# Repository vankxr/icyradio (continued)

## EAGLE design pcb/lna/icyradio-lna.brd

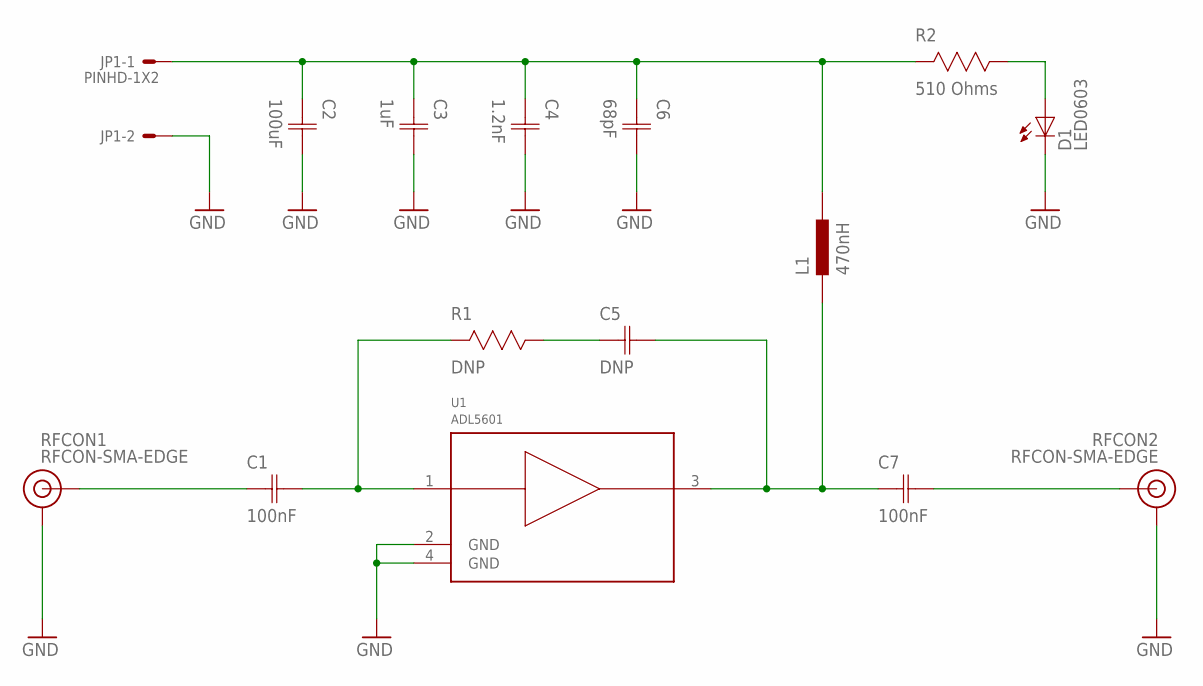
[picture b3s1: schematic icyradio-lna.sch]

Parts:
C1, C7: 100nF; CAP0603
C2: 100uF; CAP1206
C3: 1uF; CAP0603
C4: 1.2nF; CAP0603
C5: DNP; CAP0603
C6: 68pF; CAP0603
D1: LED0603; 0603
JP1: PINHD-1X2; 1X02
L1: 470nH; IND0603
R1: DNP; RES0603
R2: 510 Ohms; RES0603
RFCON1, RFCON2: RFCON-SMA-EDGE; SMA-EDGE
U1: ADL5601; SOT89

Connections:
GND: C2.2 (C2), C3.2 (C2), C4.2 (C2), C6.2 (C2), D1.C, JP1.2, RFCON1.GND@0 (GND), RFCON1.GND@1 (GND), RFCON1.GND@2 (GND), RFCON1.GND@3 (GND), RFCON2.GND@0 (GND), RFCON2.GND@1 (GND), RFCON2.GND@2 (GND), RFCON2.GND@3 (GND), U1.2 (GND), U1.4 (GND)
unnamed: C5.1 (C1), R1.1
unnamed: D1.A, R2.1
RFIN: C1.1 (C1), RFCON1.SIG (SIGNAL)
RFOUT: C7.2 (C2), RFCON2.SIG (SIGNAL)
TXPA_IN: C1.2 (C2), R1.2, U1.1 (RFIN)
TXPA_OUT: C5.2 (C2), C7.1 (C1), L1.1, U1.3 (RFOUT)
VDD: C2.1 (C1), C3.1 (C1), C4.1 (C1), C6.1 (C1), JP1.1, L1.2, R2.2

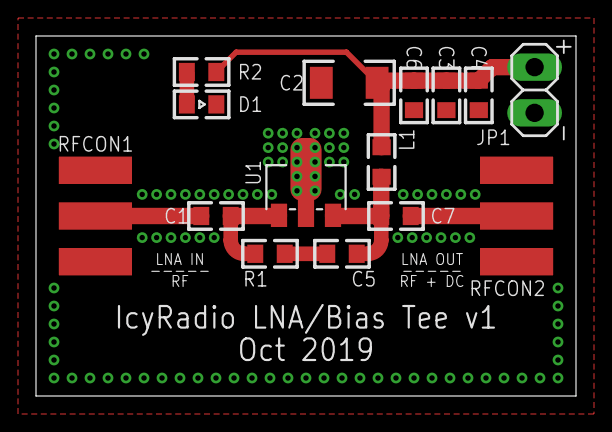
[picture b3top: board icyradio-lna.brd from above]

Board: 2 copper layers, 30.0 x 20.0 mm, 15 parts (0 on the bottom side), 8 nets.

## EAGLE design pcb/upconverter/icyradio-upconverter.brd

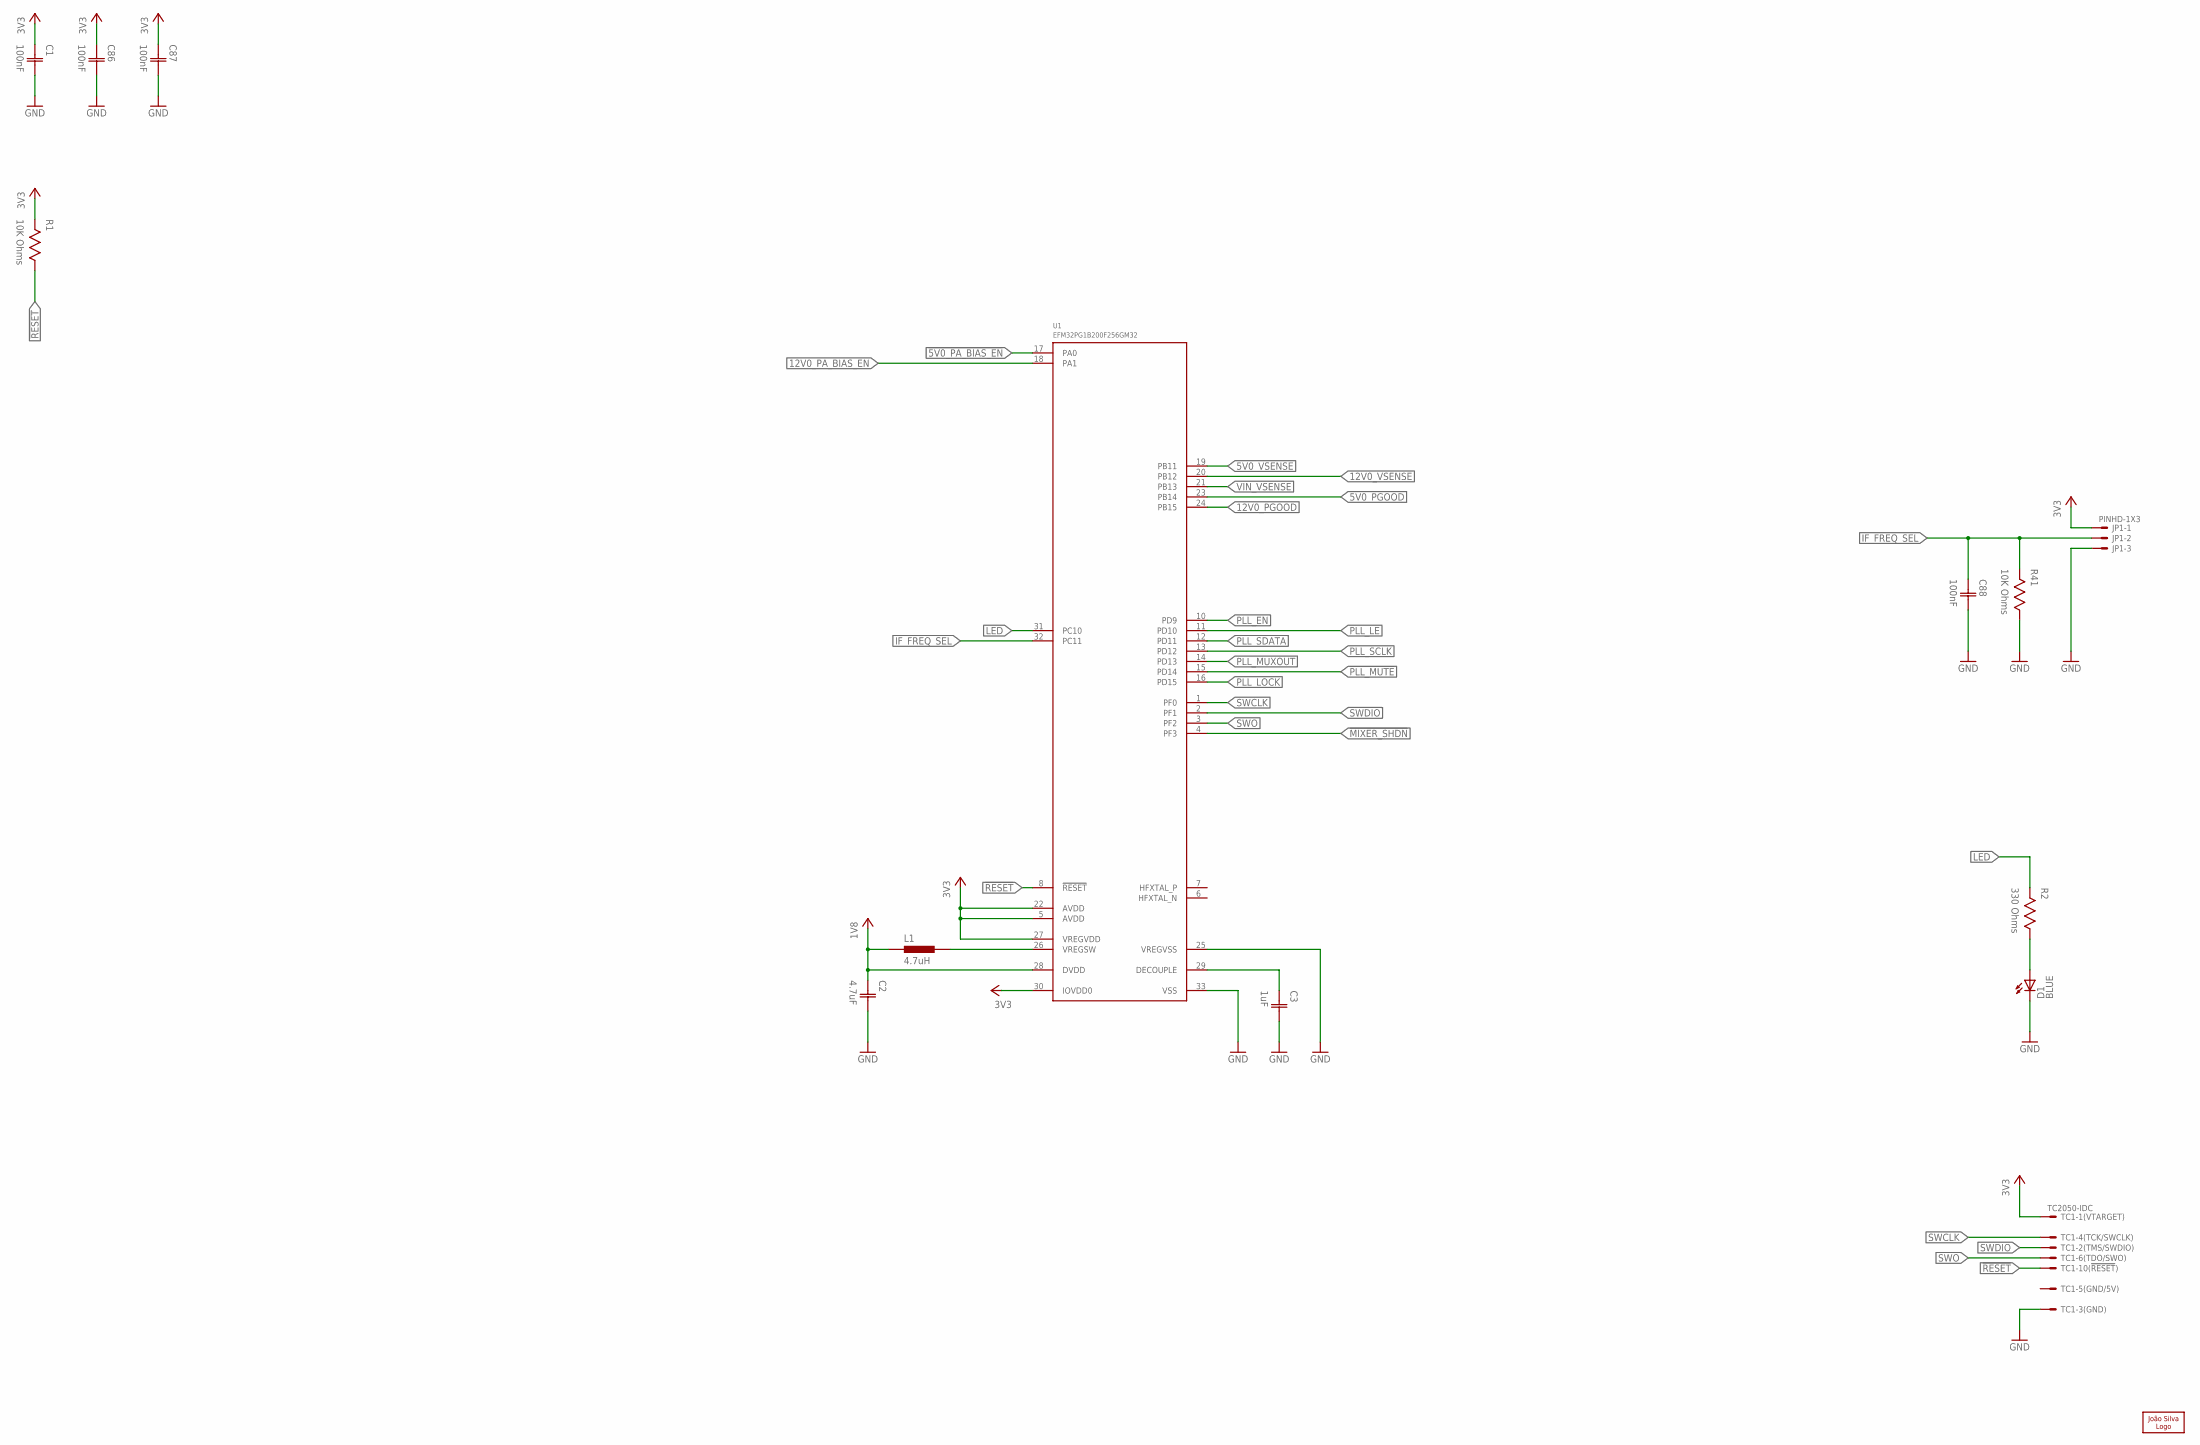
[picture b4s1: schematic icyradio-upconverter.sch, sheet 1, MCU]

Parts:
C1, C86, C87, C88: 100nF; CAP0603
C2: 4.7uF; CAP0603
C3: 1uF; CAP0603
D1: LED0603; 0603
JP1: PINHD-1X3; 1X03
L1: 4.7uH; IND0603
LOGO1: JS-5MM; JS_5MM
R1, R41: 10K Ohms; RES0603
R2: 330 Ohms; RES0603
TC1: TC2050-IDC
U1: EFM32PG1B200F256GM32; QFN32_0.5P_JPG

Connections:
1V8: C2.1 (C1), L1.1, U1.28 (DVDD)
3V3: C1.1 (C1), C86.1 (C1), C87.1 (C1), JP1.1, R1.2, TC1.1, U1.5 (AVDD), U1.22 (AVDD), U1.27 (VREGVDD), U1.30 (IOVDD0); also elsewhere on the board
5V0_PGOOD: U1.23 (PB14); also elsewhere on the board
5V0_VSENSE: U1.19 (PB11); also elsewhere on the board
12V0_PA_BIAS_EN: U1.18 (PA1); also elsewhere on the board
12V0_PGOOD: U1.24 (PB15); also elsewhere on the board
12V0_VSENSE: U1.20 (PB12); also elsewhere on the board
!5V0_PA_BIAS_EN: U1.17 (PA0); also elsewhere on the board
!MIXER_SHDN: U1.4 (PF3); also elsewhere on the board
!PLL_MUTE: U1.15 (PD14); also elsewhere on the board
!RESET: R1.1, TC1.10, U1.8 (!RESET)
GND: C1.2 (C2), C2.2 (C2), C3.2 (C2), C86.2 (C2), C87.2 (C2), C88.2 (C2), D1.C, JP1.3, R41.1, TC1.3, U1.25 (VREGVSS), U1.33 (VSS); also elsewhere on the board
IF_FREQ_SEL: C88.1 (C1), JP1.2, R41.2, U1.32 (PC11)
LED: R2.2, U1.31 (PC10)
unnamed: L1.2, U1.26 (VREGSW)
unnamed: C3.1 (C1), U1.29 (DECOUPLE)
unnamed: D1.A, R2.1
PLL_EN: U1.10 (PD9); also elsewhere on the board
PLL_LE: U1.11 (PD10); also elsewhere on the board
PLL_LOCK: U1.16 (PD15); also elsewhere on the board
PLL_MUXOUT: U1.14 (PD13); also elsewhere on the board
PLL_SCLK: U1.13 (PD12); also elsewhere on the board
PLL_SDATA: U1.12 (PD11); also elsewhere on the board
SWCLK: TC1.4, U1.1 (PF0)
SWDIO: TC1.2, U1.2 (PF1)
SWO: TC1.6, U1.3 (PF2)
VIN_VSENSE: U1.21 (PB13); also elsewhere on the board

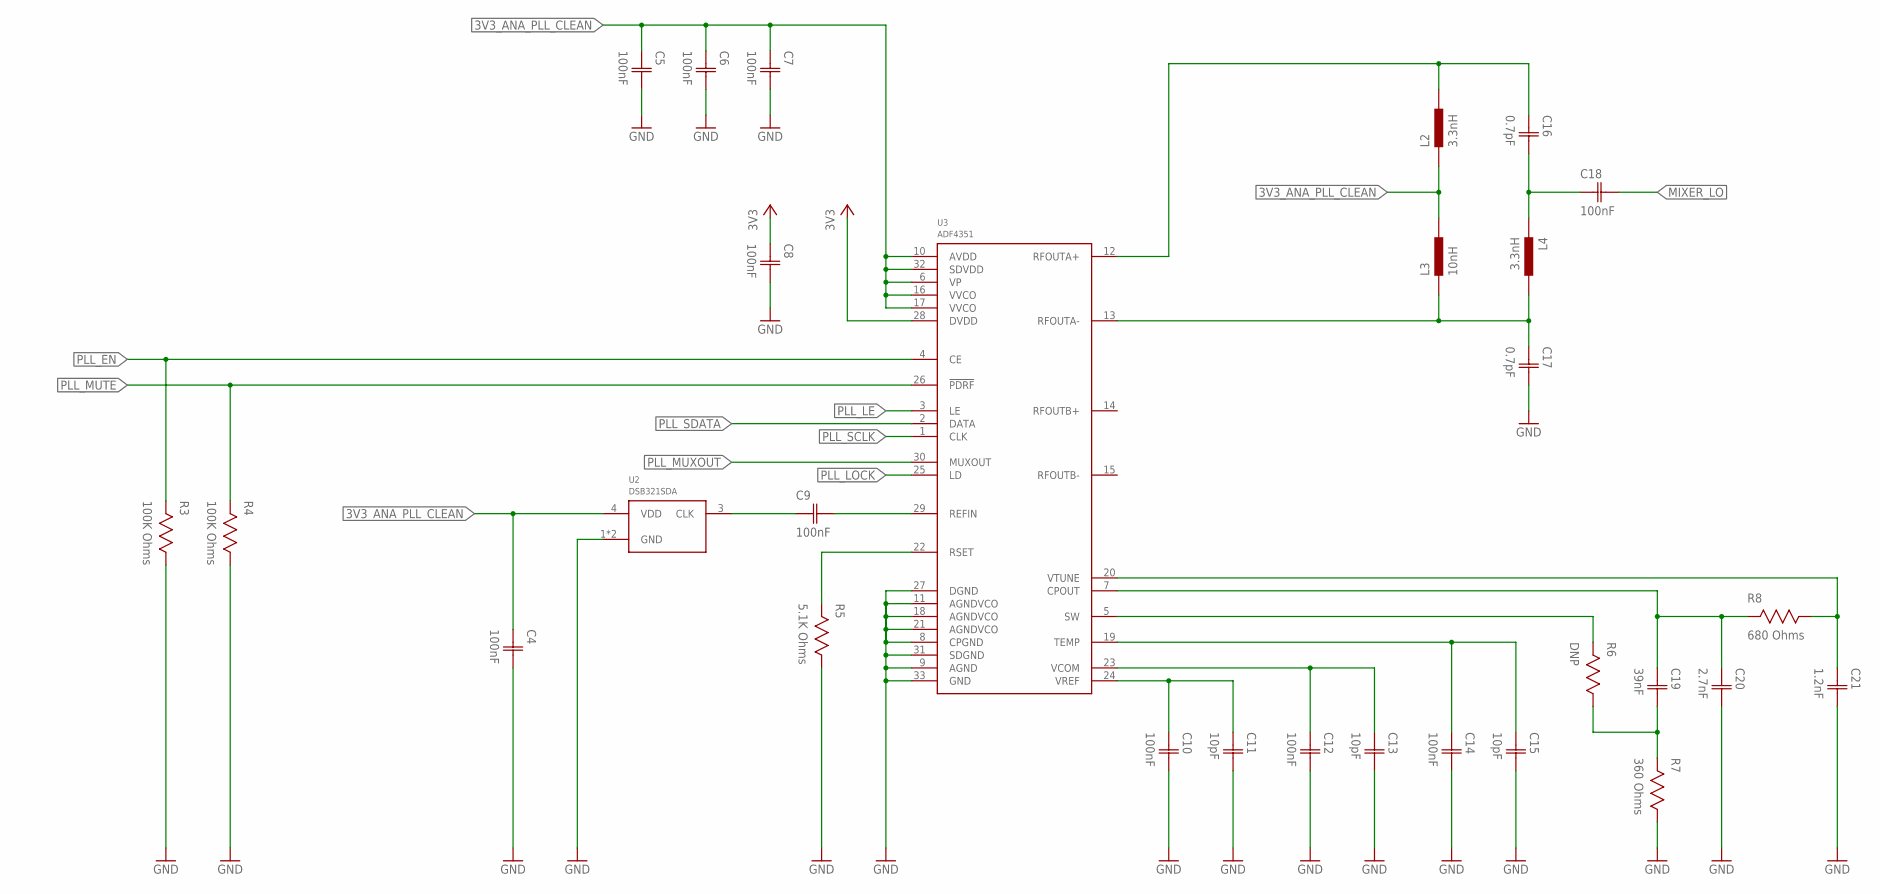
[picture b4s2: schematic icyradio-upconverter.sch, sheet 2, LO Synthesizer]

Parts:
C4, C5, C6, C7, C8, C9, C10, C12, C14, C18: 100nF; CAP0603
C11, C13, C15: 10pF; CAP0603
C16, C17: 0.7pF; CAP0603
C19: 39nF; CAP0603
C20: 2.7nF; CAP0603
C21: 1.2nF; CAP0603
L2, L4: 3.3nH; IND0603
L3: 10nH; IND0603
R3, R4: 100K Ohms; RES0603
R5: 5.1K Ohms; RES0603
R6: DNP; RES0603
R7: 360 Ohms; RES0603
R8: 680 Ohms; RES0603
U2: DSB321SDA; TCXO-3225
U3: ADF4351; QFN32

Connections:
3V3: C8.1 (C1), U3.28 (DVDD); also elsewhere on the board
3V3_ANA_PLL_CLEAN: C4.1 (C1), C5.1 (C1), C6.1 (C1), C7.1 (C1), L2.1, L3.2, U2.4 (VDD), U3.6 (VP), U3.10 (AVDD), U3.16 (VVCO), U3.17 (VVCO), U3.32 (SDVDD); also elsewhere on the board
!PLL_MUTE: R4.2, U3.26 (!PDRF); also elsewhere on the board
GND: C4.2 (C2), C5.2 (C2), C6.2 (C2), C7.2 (C2), C8.2 (C2), C10.2 (C2), C11.2 (C2), C12.2 (C2), C13.2 (C2), C14.2 (C2), C15.2 (C2), C17.2 (C2), C20.2 (C2), C21.2 (C2), R3.1, R4.1, R5.1, R7.1, U2.1 (GND), U2.2 (GND), U3.8 (CPGND), U3.9 (AGND), U3.11 (AGNDVCO), U3.18 (AGNDVCO), U3.21 (AGNDVCO), U3.27 (DGND), U3.31 (SDGND), U3.33 (GND); also elsewhere on the board
MIXER_LO: C18.2 (C2); also elsewhere on the board
unnamed: C16.2 (C2), C18.1 (C1), L4.1
unnamed: C17.1 (C1), L3.1, L4.2, U3.13 (RFOUTA-)
unnamed: C16.1 (C1), L2.2, U3.12 (RFOUTA+)
unnamed: C19.2 (C2), R6.1, R7.2
unnamed: R5.2, U3.22 (RSET)
PLL_CP_VOUT: C19.1 (C1), C20.1 (C1), R8.2, U3.7 (CPOUT)
PLL_EN: R3.2, U3.4 (CE); also elsewhere on the board
PLL_FASTLOCK_SW: R6.2, U3.5 (SW)
PLL_LE: U3.3 (LE); also elsewhere on the board
PLL_LOCK: U3.25 (LD); also elsewhere on the board
PLL_MUXOUT: U3.30 (MUXOUT); also elsewhere on the board
PLL_REF_ACC: C9.2 (C2), U3.29 (REFIN)
PLL_REF_DCC: C9.1 (C1), U2.3 (CLK)
PLL_SCLK: U3.1 (CLK); also elsewhere on the board
PLL_SDATA: U3.2 (DATA); also elsewhere on the board
PLL_TEMP: C14.1 (C1), C15.1 (C1), U3.19 (TEMP)
PLL_VCOM: C12.1 (C1), C13.1 (C1), U3.23 (VCOM)
PLL_VREF: C10.1 (C1), C11.1 (C1), U3.24 (VREF)
PLL_VTUNE: C21.1 (C1), R8.1, U3.20 (VTUNE)

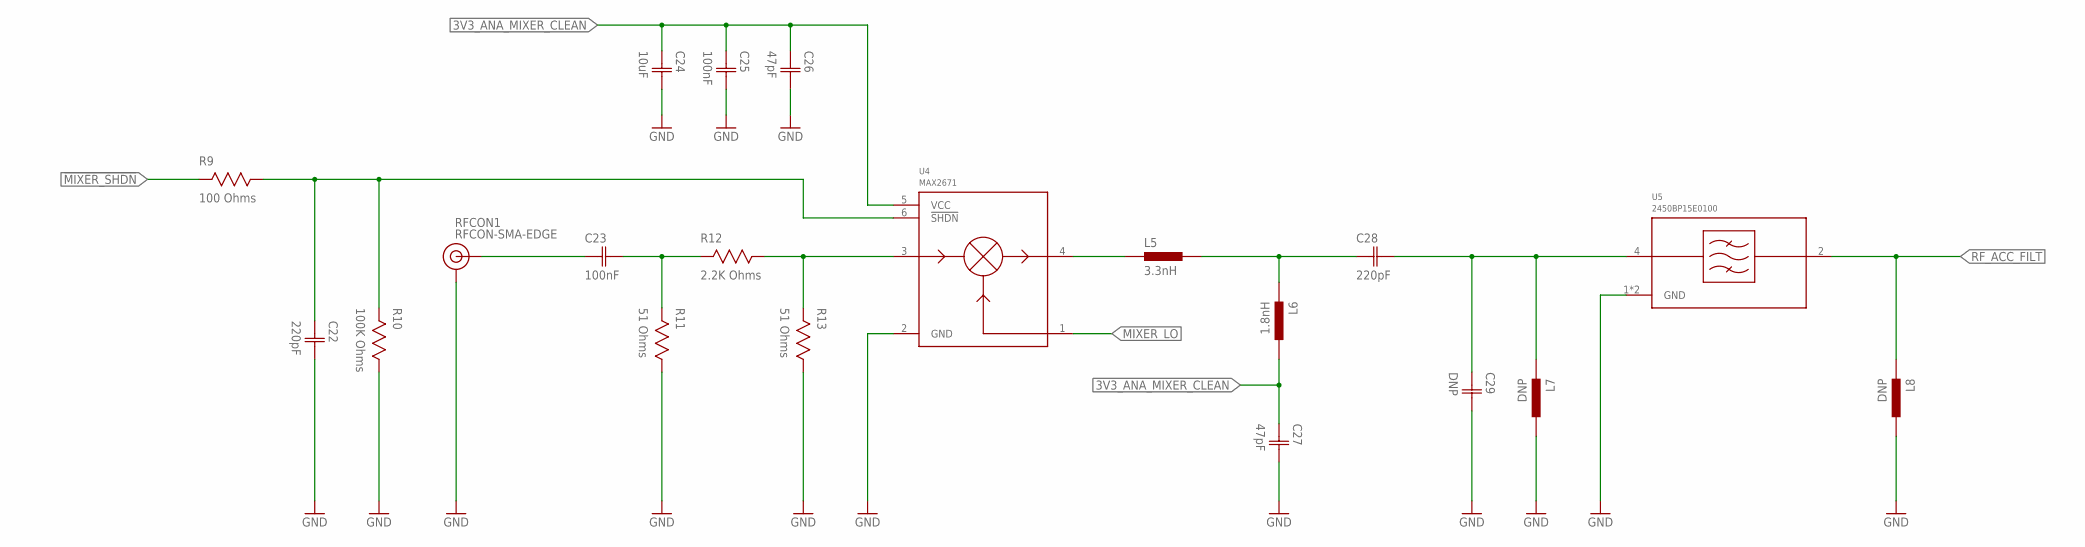
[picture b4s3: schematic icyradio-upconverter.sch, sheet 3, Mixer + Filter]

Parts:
C22, C28: 220pF; CAP0603
C23, C25: 100nF; CAP0603
C24: 10uF; CAP0603
C26, C27: 47pF; CAP0603
C29: DNP; CAP0603
L5: 3.3nH; IND0603
L6: 1.8nH; IND0603
L7, L8: DNP; IND0603
R9: 100 Ohms; RES0603
R10: 100K Ohms; RES0603
R11, R13: 51 Ohms; RES0603
R12: 2.2K Ohms; RES0603
RFCON1: RFCON-SMA-EDGE; SMA-EDGE
U4: MAX2671; SOT23-6
U5: 2450BP15E0100

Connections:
3V3_ANA_MIXER_CLEAN: C24.1 (C1), C25.1 (C1), C26.1 (C1), C27.1 (C1), L6.2, U4.5 (VCC); also elsewhere on the board
!MIXER_SHDN: R9.2; also elsewhere on the board
GND: C22.2 (C2), C24.2 (C2), C25.2 (C2), C26.2 (C2), C27.2 (C2), C29.2 (C2), L7.2, L8.2, R10.1, R11.1, R13.1, RFCON1.GND@0 (GND), RFCON1.GND@1 (GND), RFCON1.GND@2 (GND), RFCON1.GND@3 (GND), U4.2 (GND), U5.1 (GND), U5.3 (GND); also elsewhere on the board
IF_IN_ACC: R12.1, R13.2, U4.3 (IFIN)
IF_IN_DCC: C23.1 (C1), RFCON1.SIG (SIGNAL)
MIXER_LO: U4.1 (LO); also elsewhere on the board
unnamed: C22.1 (C1), R9.1, R10.2, U4.6 (!SHDN)
unnamed: C28.1 (C1), L5.2, L6.1
unnamed: L5.1, U4.4 (RFOUT)
unnamed: C23.2 (C2), R11.2, R12.2
RF_ACC: C28.2 (C2), C29.1 (C1), L7.1, U5.4 (RFIN)
RF_ACC_FILT: L8.1, U5.2 (RFOUT); also elsewhere on the board

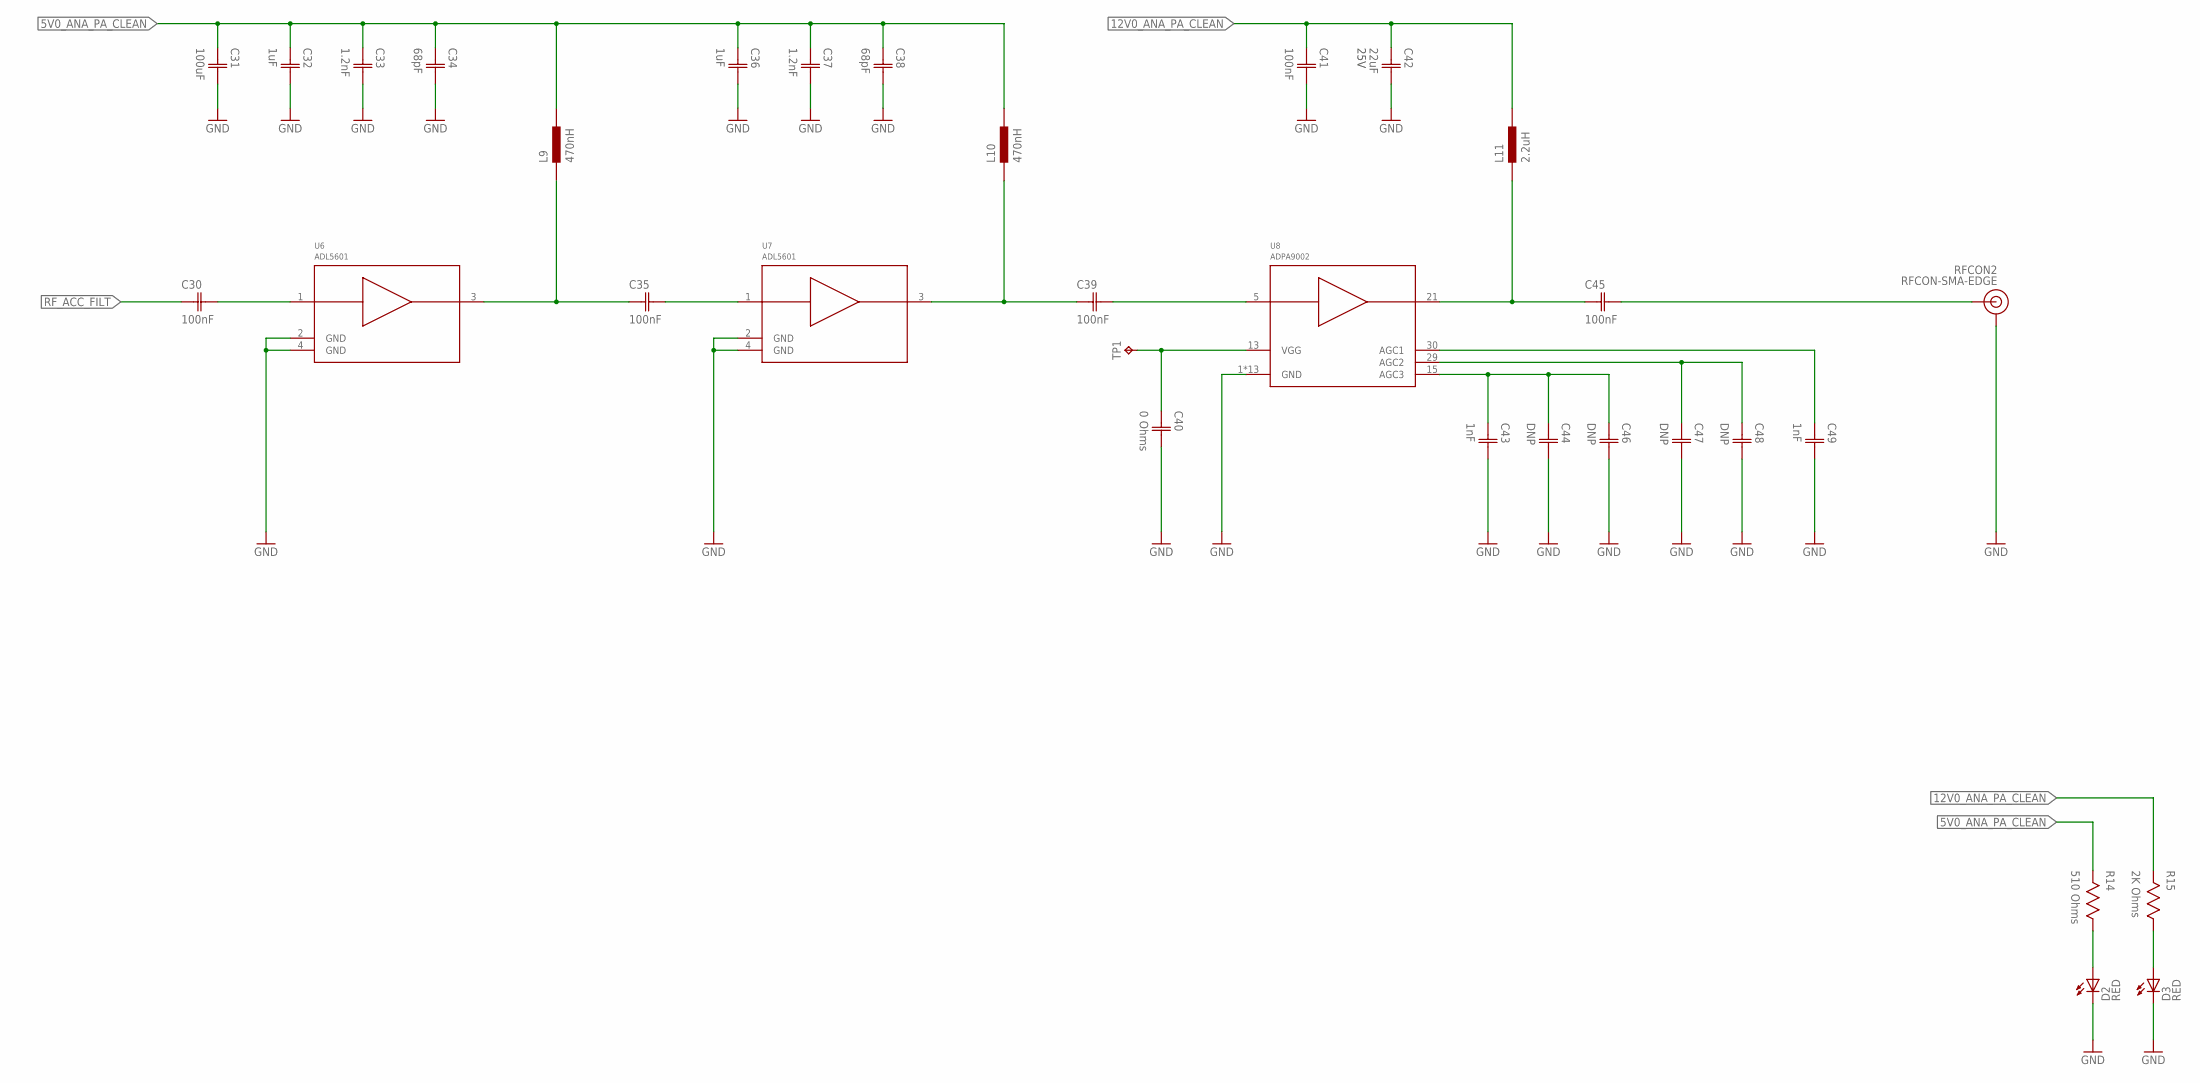
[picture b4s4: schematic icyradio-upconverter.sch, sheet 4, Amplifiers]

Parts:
C30, C35, C39, C41, C45: 100nF; CAP0603
C31: 100uF; CAP1206
C32, C36: 1uF; CAP0603
C33, C37: 1.2nF; CAP0603
C34, C38: 68pF; CAP0603
C40: 0 Ohms; CAP0603
C42: 22uF; CAP1206; VOLTAGE 25V
C43, C49: 1nF; CAP0603
C44, C46, C47, C48: DNP; CAP0603
D2, D3: LED0603; 0603
L9, L10: 470nH; IND0603
L11: 2.2uH; IND0603
R14: 510 Ohms; RES0603
R15: 2K Ohms; RES0603
RFCON2: RFCON-SMA-EDGE; SMA-EDGE
TP1: TESTPOINT-1.27MM; PAD1.27MM
U6, U7: ADL5601; SOT89
U8: ADPA9002; QFN32

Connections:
5V0_ANA_PA_CLEAN: C31.1 (C1), C32.1 (C1), C33.1 (C1), C34.1 (C1), C36.1 (C1), C37.1 (C1), C38.1 (C1), L9.2, L10.2, R14.2; also elsewhere on the board
12V0_ANA_PA_CLEAN: C41.1 (C1), C42.1 (C1), L11.2, R15.2; also elsewhere on the board
GND: C31.2 (C2), C32.2 (C2), C33.2 (C2), C34.2 (C2), C36.2 (C2), C37.2 (C2), C38.2 (C2), C40.2 (C2), C41.2 (C2), C42.2 (C2), C43.2 (C2), C44.2 (C2), C46.2 (C2), C47.2 (C2), C48.2 (C2), C49.2 (C2), D2.C, D3.C, RFCON2.GND@0 (GND), RFCON2.GND@1 (GND), RFCON2.GND@2 (GND), RFCON2.GND@3 (GND), U6.2 (GND), U6.4 (GND), U7.2 (GND), U7.4 (GND), U8.1 (GND), U8.4 (GND), U8.6 (GND), U8.8 (GND), U8.9 (GND), U8.16 (GND), U8.17 (GND), U8.20 (GND), U8.22 (GND), U8.24 (GND), U8.25 (GND), U8.32 (GND), U8.33 (GND); also elsewhere on the board
unnamed: C43.1 (C1), C44.1 (C1), C46.1 (C1), U8.15 (AGC3)
unnamed: C47.1 (C1), C48.1 (C1), U8.29 (AGC2)
unnamed: C49.1 (C1), U8.30 (AGC1)
unnamed: C40.1 (C1), TP1.TP, U8.13 (VGG)
unnamed: C30.2 (C2), U6.1 (RFIN)
unnamed: C45.1 (C1), L11.1, U8.21 (RFOUT)
unnamed: C35.1 (C1), L9.1, U6.3 (RFOUT)
unnamed: C35.2 (C2), U7.1 (RFIN)
unnamed: C39.1 (C1), L10.1, U7.3 (RFOUT)
unnamed: C39.2 (C2), U8.5 (RFIN)
unnamed: C45.2 (C2), RFCON2.SIG (SIGNAL)
unnamed: D2.A, R14.1
unnamed: D3.A, R15.1
RF_ACC_FILT: C30.1 (C1); also elsewhere on the board

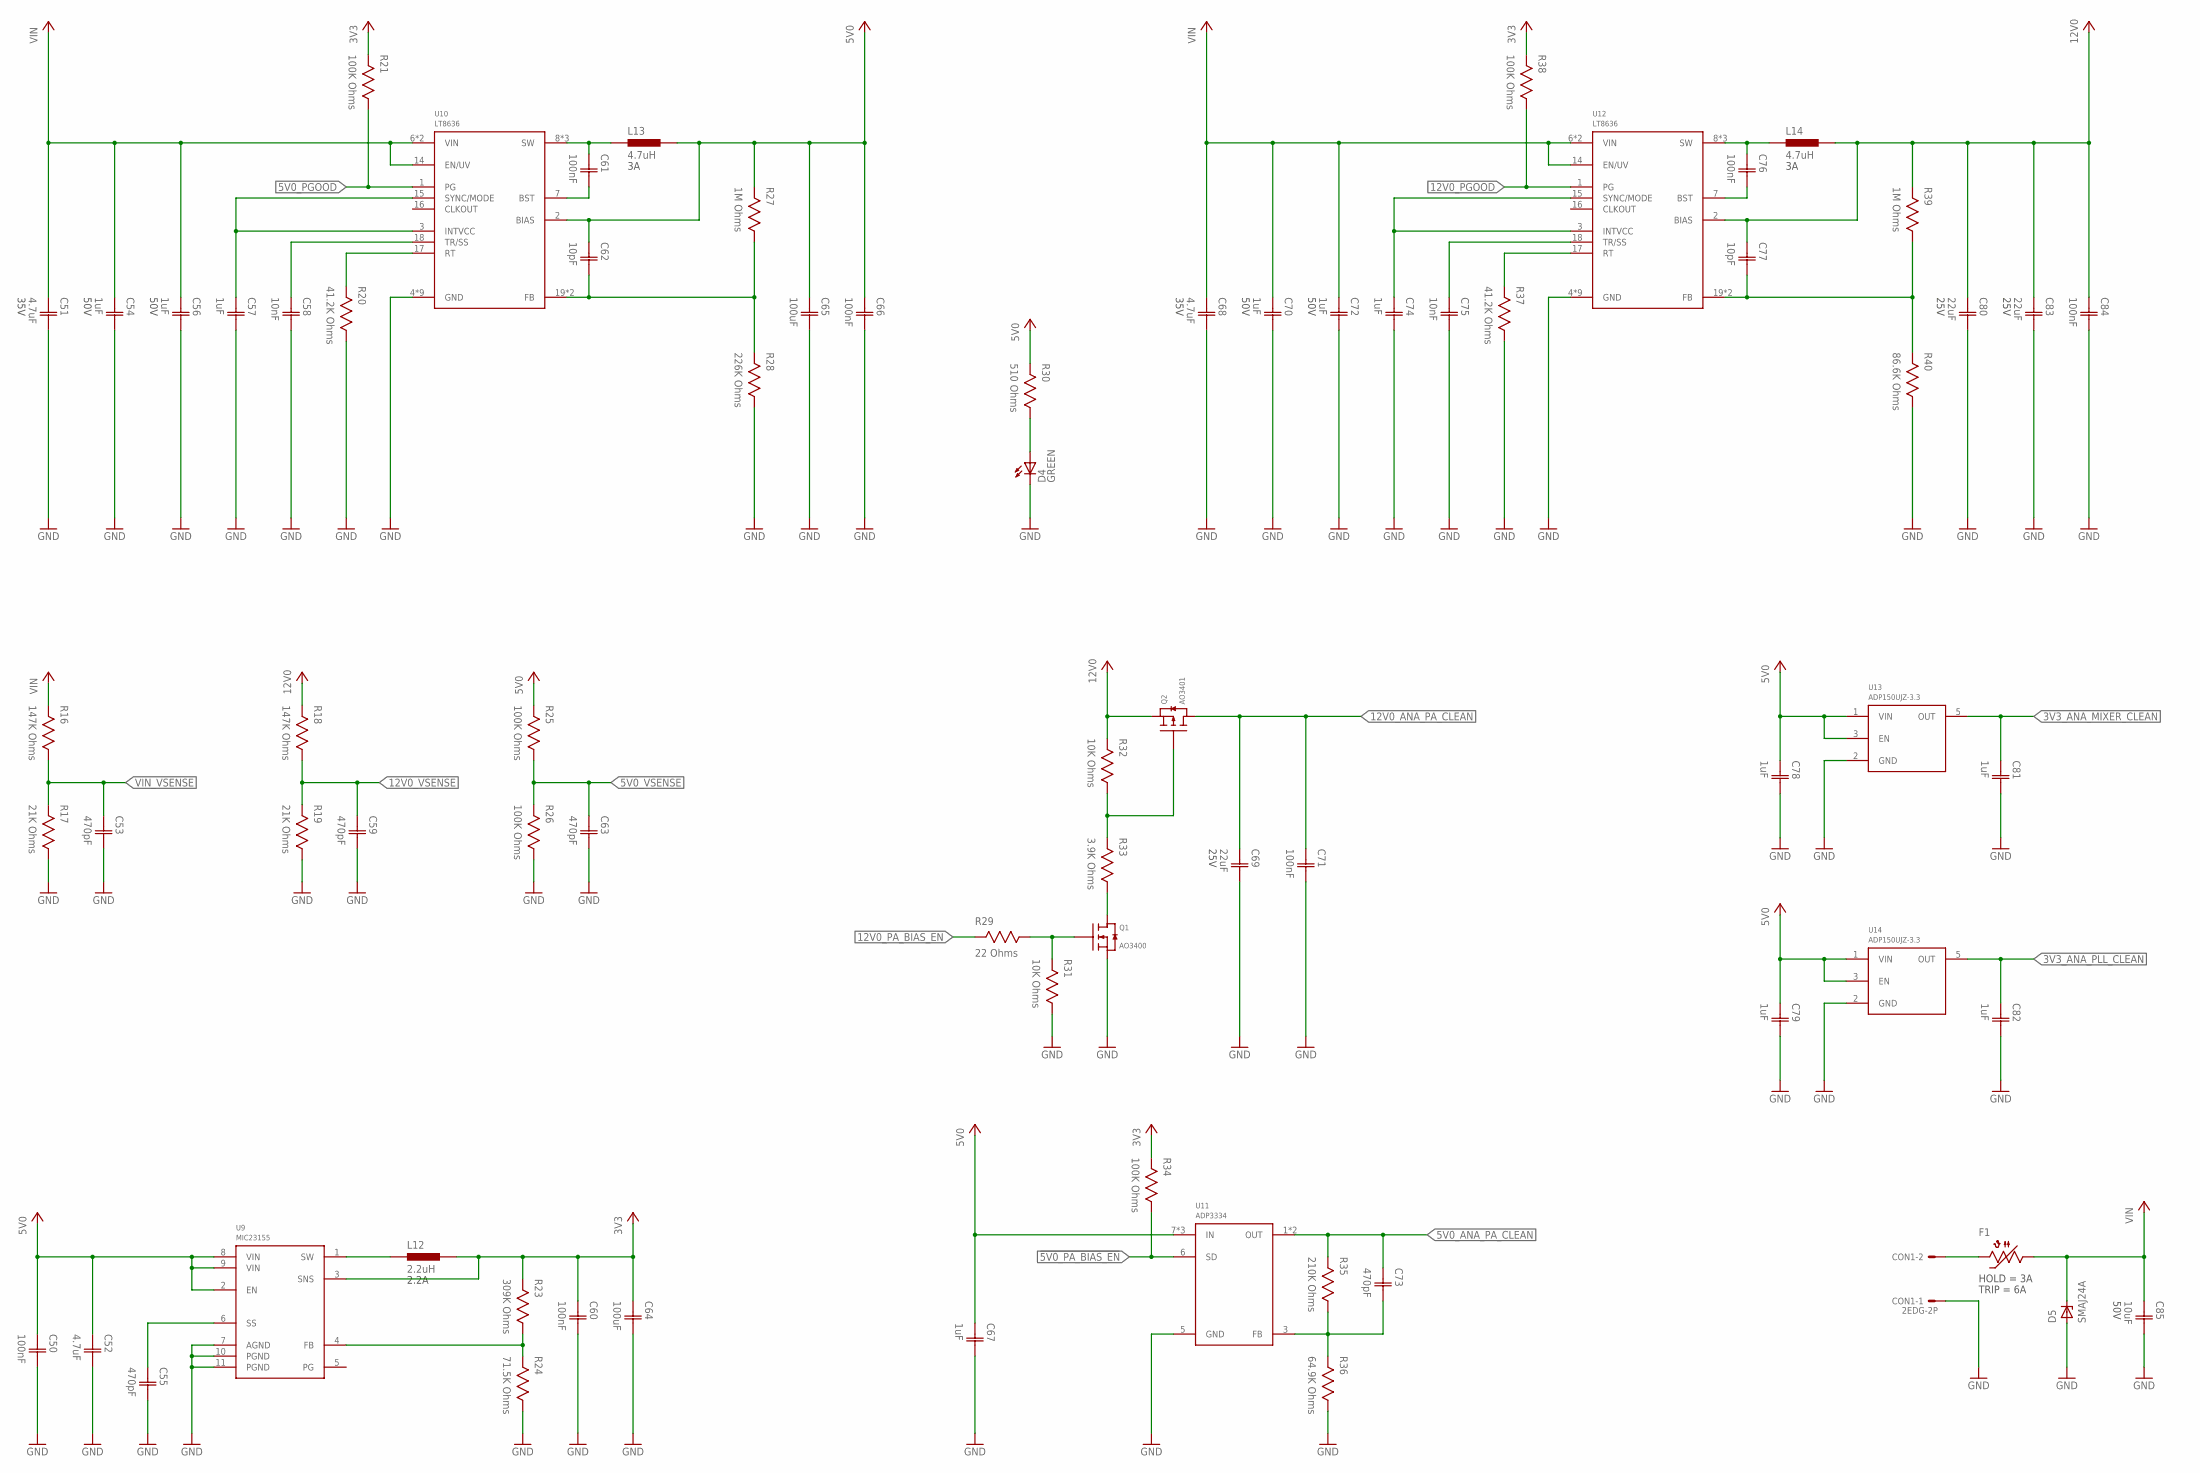
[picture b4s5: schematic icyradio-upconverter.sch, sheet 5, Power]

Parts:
C50, C60, C61, C66, C71, C76, C84: 100nF; CAP0603
C51, C68: 4.7uF; CAP0603; VOLTAGE 35V
C52: 4.7uF; CAP0603
C53, C55, C59, C63, C73: 470pF; CAP0603
C54, C56, C70, C72: 1uF; CAP0603; VOLTAGE 50V
C57, C67, C74, C78, C79, C81, C82: 1uF; CAP0603
C58, C75: 10nF; CAP0603
C62, C77: 10pF; CAP0603
C64, C65: 100uF; CAP1206
C69, C80, C83: 22uF; CAP1206; VOLTAGE 25V
C85: 10uF; CAP1206; VOLTAGE 50V
CON1: 2EDG-2P
D4: LED0603; 0603
D5: SMAJ24A; DO214AC
F1: 2.6A Hold; 1206
L12: 2.2uH; IND2520
L13, L14: 4.7uH; IND0606
Q1: AO3400; SOT23
Q2: AO3401; SOT23
R16, R18: 147K Ohms; RES0603
R17, R19: 21K Ohms; RES0603
R20, R37: 41.2K Ohms; RES0603
R21, R25, R26, R34, R38: 100K Ohms; RES0603
R23: 309K Ohms; RES0603
R24: 71.5K Ohms; RES0603
R27, R39: 1M Ohms; RES0603
R28: 226K Ohms; RES0603
R29: 22 Ohms; RES0603
R30: 510 Ohms; RES0603
R31, R32: 10K Ohms; RES0603
R33: 3.9K Ohms; RES0603
R35: 210K Ohms; RES0603
R36: 64.9K Ohms; RES0603
R40: 86.6K Ohms; RES0603
U9: MIC23155; DFN10
U10, U12: LT8636; QFN20_ASYM_CORNER
U11: ADP3334; LFCSP8_3X3
U13, U14: ADP150UJZ-3.3; SOT23-5

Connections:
3V3: C60.1 (C1), C64.1 (C1), L12.2, R21.2, R23.2, R34.2, R38.2, U9.3 (SNS); also elsewhere on the board
3V3_ANA_MIXER_CLEAN: C81.1 (C1), U13.5 (OUT); also elsewhere on the board
3V3_ANA_PLL_CLEAN: C82.1 (C1), U14.5 (OUT); also elsewhere on the board
3V3_FB: R23.1, R24.2, U9.4 (FB)
3V3_SOFTSTART: C55.1 (C1), U9.6 (SS)
3V3_SW: L12.1, U9.1 (SW)
5V0: C50.1 (C1), C52.1 (C1), C62.1 (C1), C65.1 (C1), C66.1 (C1), C67.1 (C1), C78.1 (C1), C79.1 (C1), L13.2, R25.2, R27.2, R30.2, U9.2 (EN), U9.8 (VIN), U9.9 (VIN), U10.2 (BIAS), U11.7 (IN), U11.8 (IN), U11.9 (IN), U13.1 (VIN), U13.3 (EN), U14.1 (VIN), U14.3 (EN)
5V0_ANA_PA_CLEAN: C73.1 (C1), R35.2, U11.1 (OUT), U11.2 (OUT); also elsewhere on the board
5V0_BST: C61.2 (C2), U10.7 (BST)
5V0_FB: C62.2 (C2), R27.1, R28.2, U10.19 (FB), U10.20 (FB)
5V0_INTVCC: C57.1 (C1), U10.3 (INTVCC), U10.15 (SYNC/MODE)
5V0_PGOOD: R21.1, U10.1 (PG); also elsewhere on the board
5V0_RT: R20.2, U10.17 (RT)
5V0_SS: C58.1 (C1), U10.18 (TR/SS)
5V0_SW: C61.1 (C1), L13.1, U10.8 (SW), U10.9 (SW), U10.10 (SW)
5V0_VSENSE: C63.1 (C1), R25.1, R26.2; also elsewhere on the board
12V0: C77.1 (C1), C80.1 (C1), C83.1 (C1), C84.1 (C1), L14.2, Q2.2 (S), R18.2, R32.2, R39.2, U12.2 (BIAS)
12V0_ANA_PA_CLEAN: C69.1 (C1), C71.1 (C1), Q2.3 (D); also elsewhere on the board
12V0_BST: C76.2 (C2), U12.7 (BST)
12V0_FB: C77.2 (C2), R39.1, R40.2, U12.19 (FB), U12.20 (FB)
12V0_INTVCC: C74.1 (C1), U12.3 (INTVCC), U12.15 (SYNC/MODE)
12V0_PA_BIAS_EN: R29.2; also elsewhere on the board
12V0_PGOOD: R38.1, U12.1 (PG); also elsewhere on the board
12V0_RT: R37.2, U12.17 (RT)
12V0_SS: C75.1 (C1), U12.18 (TR/SS)
12V0_SW: C76.1 (C1), L14.1, U12.8 (SW), U12.9 (SW), U12.10 (SW)
12V0_VSENSE: C59.1 (C1), R18.1, R19.2; also elsewhere on the board
!5V0_PA_BIAS_EN: R34.1, U11.6 (SD); also elsewhere on the board
GND: C50.2 (C2), C51.2 (C2), C52.2 (C2), C53.2 (C2), C54.2 (C2), C55.2 (C2), C56.2 (C2), C57.2 (C2), C58.2 (C2), C59.2 (C2), C60.2 (C2), C63.2 (C2), C64.2 (C2), C65.2 (C2), C66.2 (C2), C67.2 (C2), C68.2 (C2), C69.2 (C2), C70.2 (C2), C71.2 (C2), C72.2 (C2), C74.2 (C2), C75.2 (C2), C78.2 (C2), C79.2 (C2), C80.2 (C2), C81.2 (C2), C82.2 (C2), C83.2 (C2), C84.2 (C2), C85.2 (C2), CON1.P$1, D4.C, D5.A, Q1.2 (S), R17.1, R19.1, R20.1, R24.1, R26.1, R28.1, R31.1, R36.1, R37.1, R40.1, U9.7 (AGND), U9.10 (PGND), U9.11 (PGND), U10.4 (GND), U10.5 (GND), U10.12 (GND), U10.13 (GND), U10.21 (GND), U10.M1 (GND), U10.M2 (GND), U10.M3 (GND), U10.M4 (GND), U11.5 (GND), U12.4 (GND), U12.5 (GND), U12.12 (GND), U12.13 (GND), U12.21 (GND), U12.M1 (GND), U12.M2 (GND), U12.M3 (GND), U12.M4 (GND), U13.2 (GND), U14.2 (GND); also elsewhere on the board
unnamed: Q1.1 (G), R29.1, R31.2
unnamed: Q2.1 (G), R32.1, R33.2
unnamed: Q1.3 (D), R33.1
unnamed: CON1.P$2, F1.2
unnamed: C73.2 (C2), R35.1, R36.2, U11.3 (FB)
unnamed: D4.A, R30.1
VIN: C51.1 (C1), C54.1 (C1), C56.1 (C1), C68.1 (C1), C70.1 (C1), C72.1 (C1), C85.1 (C1), D5.C, F1.1, R16.2, U10.6 (VIN), U10.11 (VIN), U10.14 (EN/UV), U12.6 (VIN), U12.11 (VIN), U12.14 (EN/UV)
VIN_VSENSE: C53.1 (C1), R16.1, R17.2; also elsewhere on the board

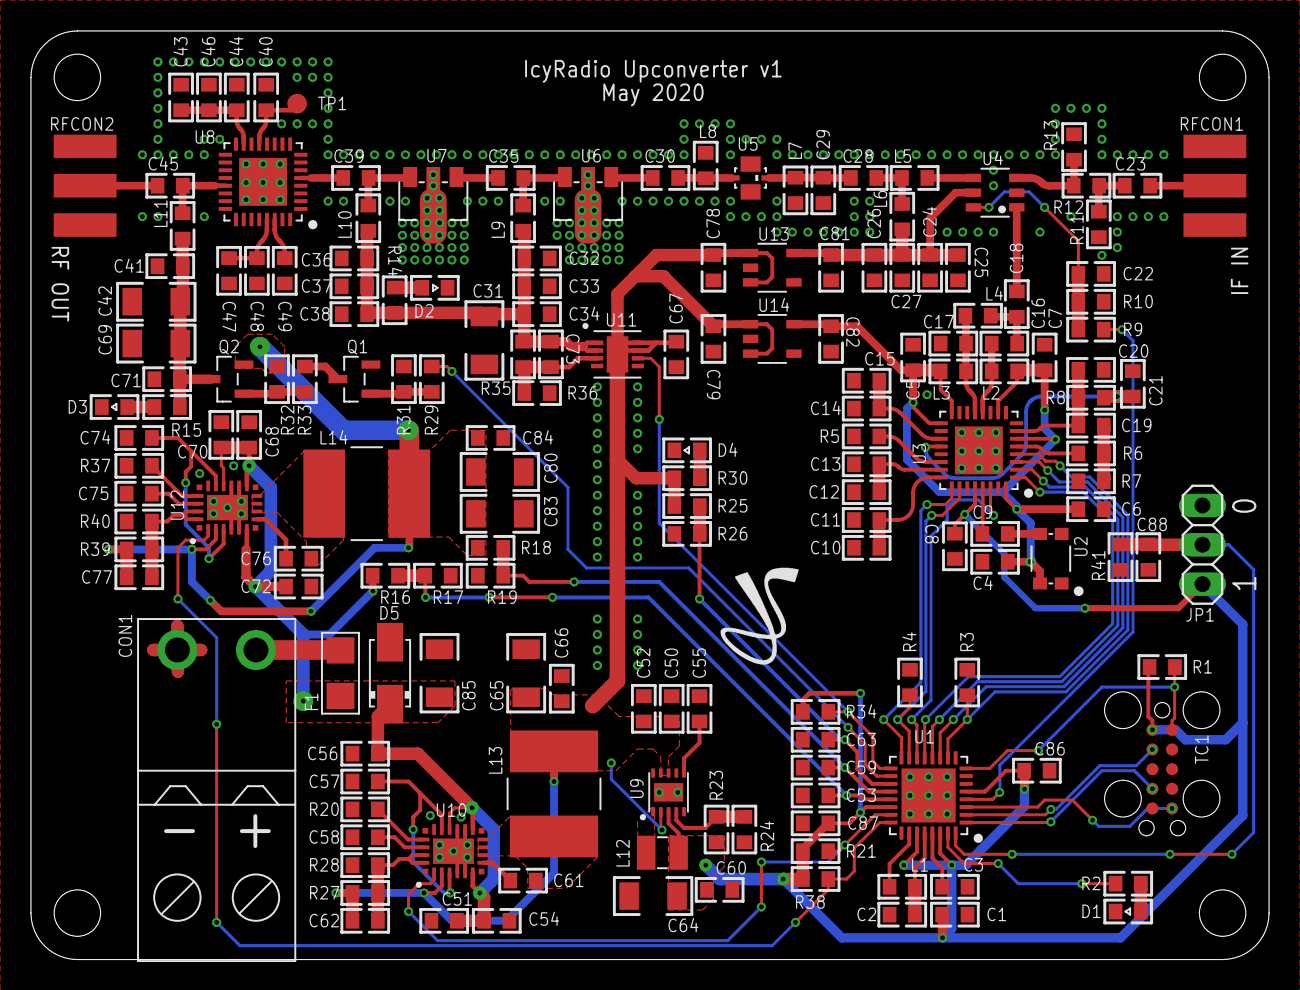
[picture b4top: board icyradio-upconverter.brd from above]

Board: 2 copper layers, 80.0 x 60.0 mm, 171 parts (0 on the bottom side), 90 nets.
